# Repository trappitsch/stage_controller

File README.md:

# Stage controller

Multi-axis stage controller repo.

## Crates

The project is divided into multiple crates.
The following list gives an overview.

- `axis_control`: Controls a single axis of a stage.
- `rp2350`: Firmware for stage controller running on an RP2350.
- `icd`: Interface control document: How the device talks to the host.

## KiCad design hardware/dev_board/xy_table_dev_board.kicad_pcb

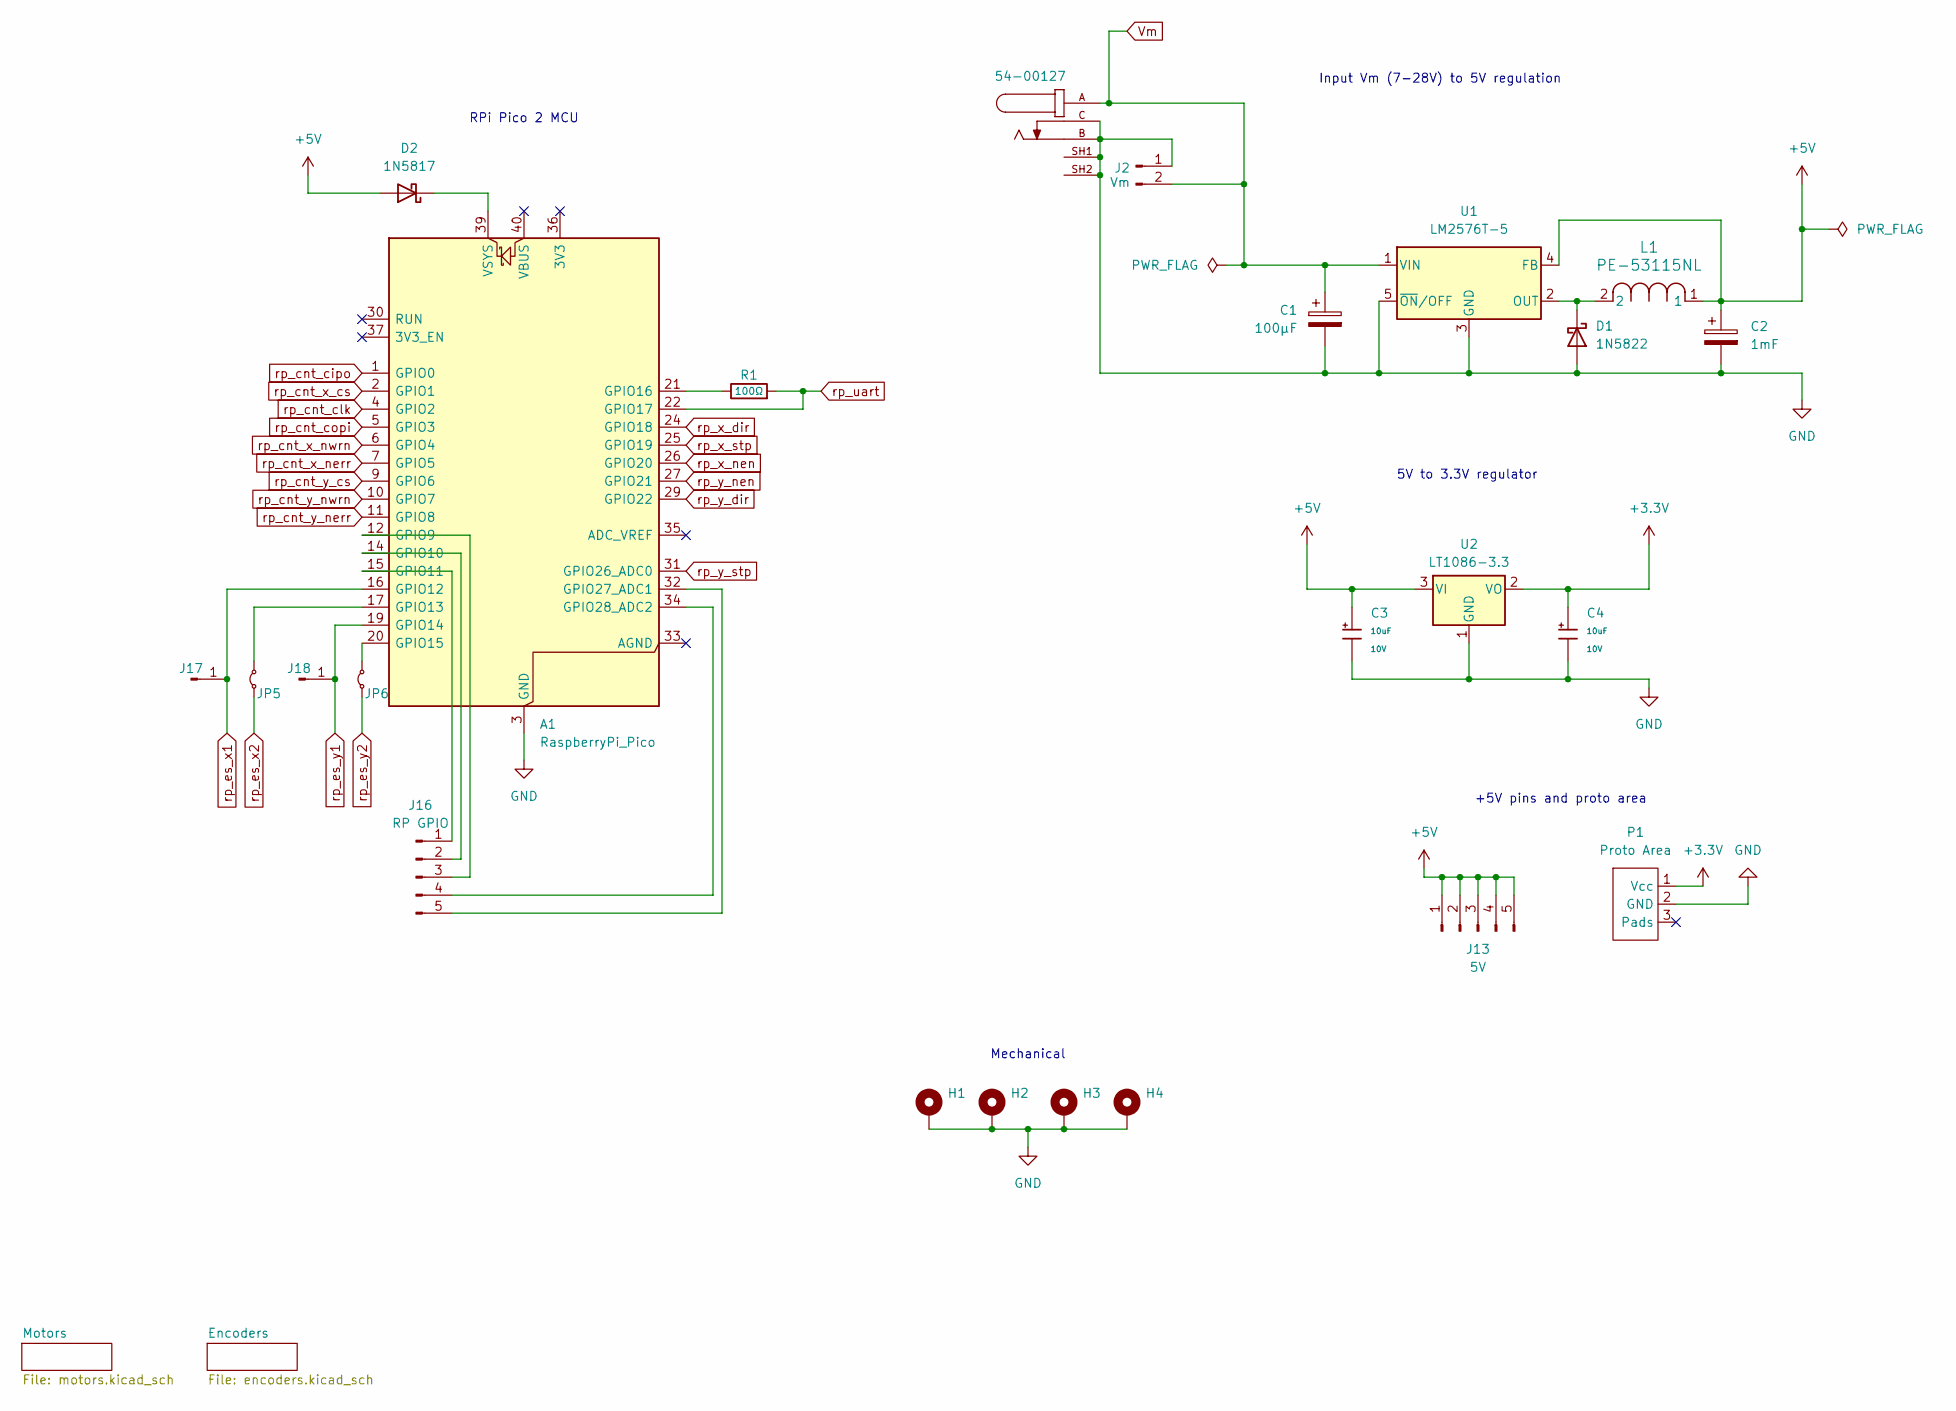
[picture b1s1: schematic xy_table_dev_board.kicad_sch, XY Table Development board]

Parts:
A1: RaspberryPi_Pico; RaspberryPi_Pico_Common_Unspecified
C1: 100µF; CP_Radial_D6.3mm_P2.50mm; Digikey 732-9215-1-ND
C2: 1mF; CP_Radial_D12.5mm_P5.00mm; Digikey 493-1322-ND
C3, C4: 10uF; C_1206_3216Metric_Pad1.33x1.80mm_HandSolder; Rated Voltage 10V; Digikey 478-11220-2-ND
D1: 1N5822; D_DO-201AD_P15.24mm_Horizontal; Digikey 497-11370-1-ND
D2: 1N5817; D_DO-41_SOD81_P10.16mm_Horizontal
H1, H2, H3, H4: MountingHole_Pad; MountingHole_3.2mm_M3_DIN965_Pad_TopBottom
J1: 54-00127; TENSILITY_54-00127; PARTREV A; Digikey 839-54-00127-ND
J2: Vm; PinHeader_1x02_P2.54mm_Vertical
J13: 5V; PinHeader_1x05_P2.54mm_Vertical
J16: RP GPIO; PinHeader_1x05_P2.54mm_Vertical
J17, J18: Conn_01x01_Pin; PinHeader_1x01_P2.54mm_Vertical
JP5, JP6: Jumper_2_Small_Bridged; TestPoint_2Pads_Pitch2.54mm_Drill0.8mm
L1: PE-53115NL; IND_PE-53115NL_PUL; Digikey 553-1566-5-ND
P1: Proto Area; proto_area_5x20_vcc_gnd
R1: 100Ω; R_1206_3216Metric_Pad1.30x1.75mm_HandSolder
U1: LM2576T-5; TO-220-5_Vertical; Digikey LM2576T-5.0/NOPB-ND
U2: LT1086-3.3; TO-220-3_Vertical

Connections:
+3.3V: C4.1, P1.1 (Vcc), U2.2 (VO); also elsewhere on the board
+5V: C2.1, C3.1, D2.2 (A), J13.1, J13.2, J13.3, J13.4, J13.5, L1.1, U1.4 (FB), U2.3 (VI); also elsewhere on the board
GND: A1.3 (GND), A1.8 (GND), A1.13 (GND), A1.18 (GND), A1.23 (GND), A1.28 (GND), A1.38 (GND), C1.2, C2.2, C3.2, C4.2, D1.2 (A), H1.1 (1_1), H2.1 (1_1), H3.1 (1_1), H4.1 (1_1), J1.B, J1.C, J1.SH1, J1.SH2, J2.1, P1.2 (GND), U1.3 (GND), U1.5 (~ON/OFF), U2.1 (GND); also elsewhere on the board
unnamed: A1.12 (GPIO9), J16.3
unnamed: A1.14 (GPIO10), J16.2
unnamed: A1.15 (GPIO11), J16.1
unnamed: A1.17 (GPIO13), JP5.2 (B)
unnamed: A1.20 (GPIO15), JP6.2 (B)
unnamed: A1.21 (GPIO16), R1.1
unnamed: A1.32 (GPIO27_ADC1), J16.5
unnamed: A1.34 (GPIO28_ADC2), J16.4
unnamed: A1.39 (VSYS), D2.1 (K)
unnamed: D1.1 (K), L1.2, U1.2 (OUT)
Vm: C1.1, J1.A, J2.2, U1.1 (VIN); also elsewhere on the board
rp_cnt_cipo: A1.1 (GPIO0); also elsewhere on the board
rp_cnt_clk: A1.4 (GPIO2); also elsewhere on the board
rp_cnt_copi: A1.5 (GPIO3); also elsewhere on the board
rp_cnt_x_cs: A1.2 (GPIO1); also elsewhere on the board
rp_cnt_x_nerr: A1.7 (GPIO5); also elsewhere on the board
rp_cnt_x_nwrn: A1.6 (GPIO4); also elsewhere on the board
rp_cnt_y_cs: A1.9 (GPIO6); also elsewhere on the board
rp_cnt_y_nerr: A1.11 (GPIO8); also elsewhere on the board
rp_cnt_y_nwrn: A1.10 (GPIO7); also elsewhere on the board
rp_es_x1: A1.16 (GPIO12), J17.1 (Pin_1_1); also elsewhere on the board
rp_es_x2: JP5.1 (A); also elsewhere on the board
rp_es_y1: A1.19 (GPIO14), J18.1 (Pin_1_1); also elsewhere on the board
rp_es_y2: JP6.1 (A); also elsewhere on the board
rp_uart: A1.22 (GPIO17), R1.2; also elsewhere on the board
rp_x_dir: A1.24 (GPIO18); also elsewhere on the board
rp_x_nen: A1.26 (GPIO20); also elsewhere on the board
rp_x_stp: A1.25 (GPIO19); also elsewhere on the board
rp_y_dir: A1.29 (GPIO22); also elsewhere on the board
rp_y_nen: A1.27 (GPIO21); also elsewhere on the board
rp_y_stp: A1.31 (GPIO26_ADC0); also elsewhere on the board

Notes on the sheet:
RPi Pico 2 MCU
Input Vm (7-28V) to 5V regulation
+5V pins and proto area
5V to 3.3V regulator
Mechanical

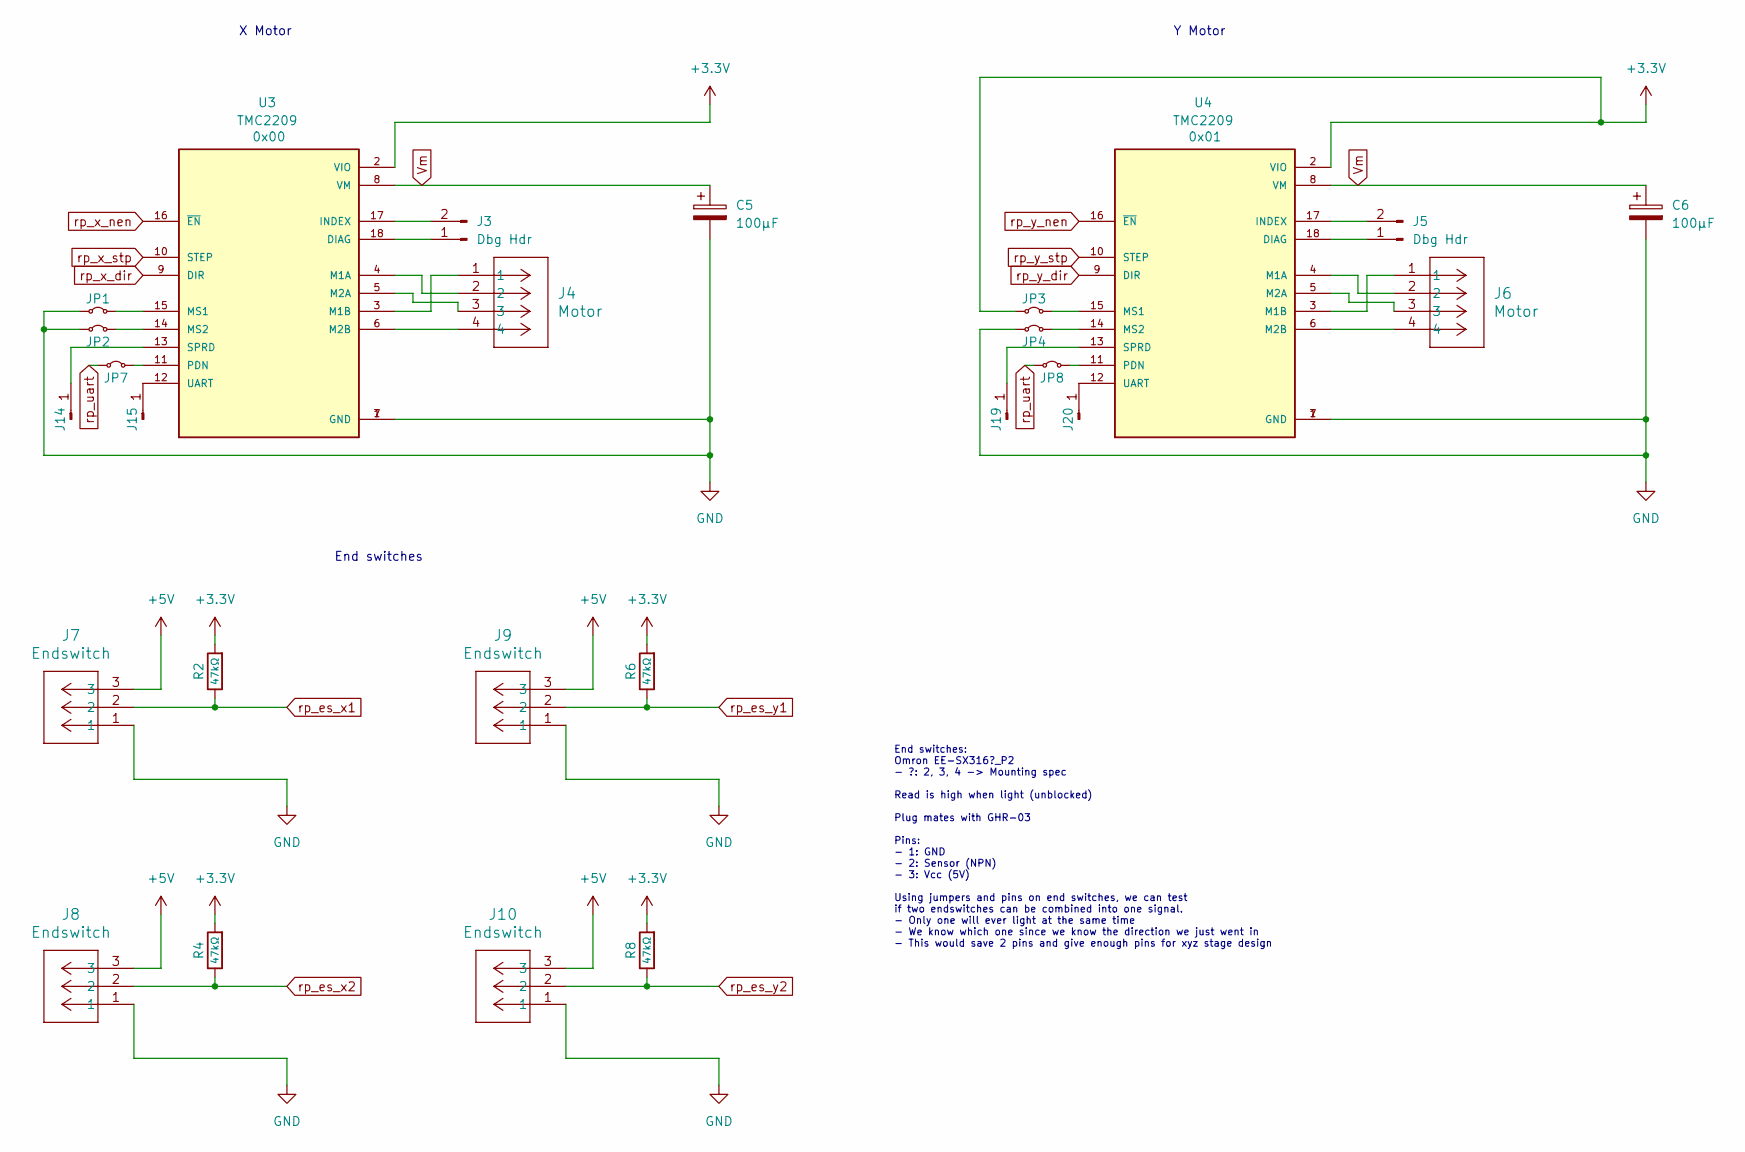
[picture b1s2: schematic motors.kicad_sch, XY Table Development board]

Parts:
C5, C6: 100µF; CP_Radial_D6.3mm_P2.50mm; Digikey 732-9215-1-ND
J3, J5: Dbg Hdr; PinHeader_1x02_P2.54mm_Vertical
J4, J6: Motor; CONN_A-6373-04A_MOL; Digikey WM2702-ND
J7, J8, J9, J10: Endswitch; CONN_A-6373-03A_MOL; Digikey WM2701-ND
J14, J15, J19, J20: Conn_01x01_Pin; PinHeader_1x01_P2.54mm_Vertical
JP1, JP2, JP3, JP4, JP7, JP8: Jumper_2_Small_Bridged; TestPoint_2Pads_Pitch2.54mm_Drill0.8mm
R2, R4, R6, R8: 47kΩ; R_Axial_DIN0207_L6.3mm_D2.5mm_P7.62mm_Horizontal; Digikey CF18JT47K0TR-ND
U3, U4: TMC2209; MODULE_TMC2209_SILENTSTEPSTICK; PARTREV 1.20

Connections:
+3.3V: JP3.1 (A), R2.2, R4.2, R6.2, R8.2, U3.2 (VIO), U4.2 (VIO); also elsewhere on the board
+5V: J7.3, J8.3, J9.3, J10.3; also elsewhere on the board
GND: C5.2, C6.2, J7.1, J8.1, J9.1, J10.1, JP1.1 (A), JP2.1 (A), JP4.1 (A), U3.1 (GND), U3.7 (GND), U4.1 (GND), U4.7 (GND); also elsewhere on the board
unnamed: J3.1, U3.18 (DIAG)
unnamed: J3.2, U3.17 (INDEX)
unnamed: J5.1, U4.18 (DIAG)
unnamed: J5.2, U4.17 (INDEX)
unnamed: J14.1 (Pin_1_1), U3.13 (SPRD)
unnamed: J15.1 (Pin_1_1), U3.12 (UART)
unnamed: J19.1 (Pin_1_1), U4.13 (SPRD)
unnamed: J20.1 (Pin_1_1), U4.12 (UART)
unnamed: JP1.2 (B), U3.15 (MS1)
unnamed: JP2.2 (B), U3.14 (MS2)
unnamed: JP3.2 (B), U4.15 (MS1)
unnamed: JP4.2 (B), U4.14 (MS2)
unnamed: JP7.2 (B), U3.11 (PDN)
unnamed: JP8.2 (B), U4.11 (PDN)
unnamed: J4.2, U3.4 (M1A)
unnamed: J4.1, U3.3 (M1B)
unnamed: J4.3, U3.5 (M2A)
unnamed: J4.4, U3.6 (M2B)
unnamed: J6.2, U4.4 (M1A)
unnamed: J6.1, U4.3 (M1B)
unnamed: J6.3, U4.5 (M2A)
unnamed: J6.4, U4.6 (M2B)
Vm: C5.1, C6.1, U3.8 (VM), U4.8 (VM); also elsewhere on the board
rp_es_x1: J7.2, R2.1; also elsewhere on the board
rp_es_x2: J8.2, R4.1; also elsewhere on the board
rp_es_y1: J9.2, R6.1; also elsewhere on the board
rp_es_y2: J10.2, R8.1; also elsewhere on the board
rp_uart: JP7.1 (A), JP8.1 (A); also elsewhere on the board
rp_x_dir: U3.9 (DIR); also elsewhere on the board
rp_x_nen: U3.16 (~EN); also elsewhere on the board
rp_x_stp: U3.10 (STEP); also elsewhere on the board
rp_y_dir: U4.9 (DIR); also elsewhere on the board
rp_y_nen: U4.16 (~EN); also elsewhere on the board
rp_y_stp: U4.10 (STEP); also elsewhere on the board

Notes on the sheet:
Y Motor
End switches: Omron EE-SX316?_P2 - ?: 2, 3, 4 -> Mounting spec Read is high when light (unblocked) Plug mates with GHR-03 Pins: - 1: GND - 2: Sensor (NPN) - 3: Vcc (5V) Using jumpers and pins on end switches, we can test if two endswitches can be combined into one signal. - Only one will ever light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
End switches
X Motor

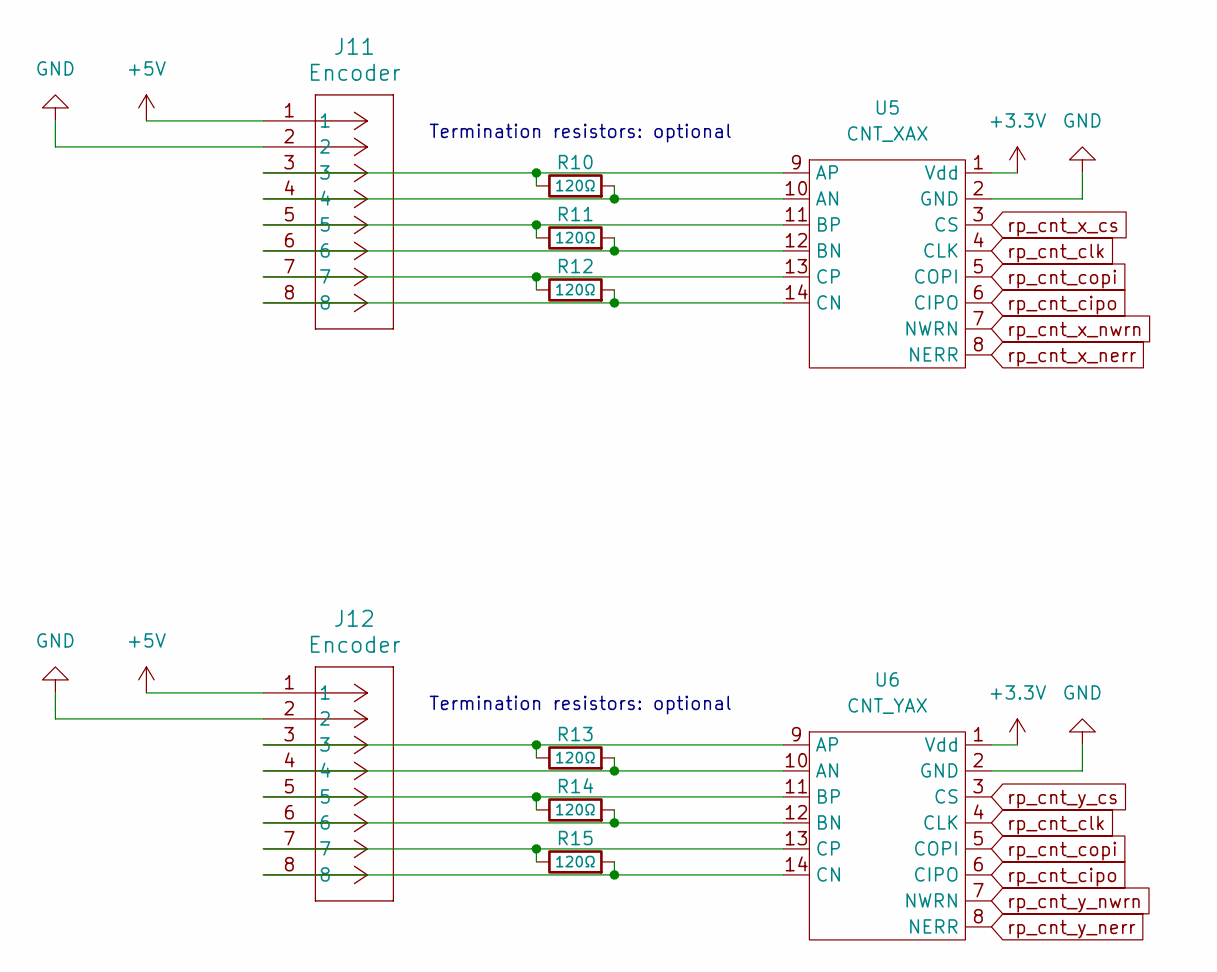
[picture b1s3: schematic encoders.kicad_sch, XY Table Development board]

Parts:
J11, J12: Encoder; CONN_A-6373-08A_MOL; Digikey 900-0022112082-ND
R10, R11, R12, R13, R14, R15: 120Ω; R_Axial_DIN0207_L6.3mm_D2.5mm_P7.62mm_Horizontal
U5: CNT_XAX; iC-MD_brd_5VSig_3.3Vcc
U6: CNT_YAX; iC-MD_brd_5VSig_3.3Vcc

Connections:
+3.3V: U5.1 (Vdd), U6.1 (Vdd); also elsewhere on the board
+5V: J11.1, J12.1; also elsewhere on the board
GND: J11.2, J12.2, U5.2 (GND), U6.2 (GND); also elsewhere on the board
unnamed: J11.4, R10.2, U5.10 (AN)
unnamed: J11.3, R10.1, U5.9 (AP)
unnamed: J11.6, R11.2, U5.12 (BN)
unnamed: J11.5, R11.1, U5.11 (BP)
unnamed: J11.8, R12.2, U5.14 (CN)
unnamed: J11.7, R12.1, U5.13 (CP)
unnamed: J12.4, R13.2, U6.10 (AN)
unnamed: J12.3, R13.1, U6.9 (AP)
unnamed: J12.6, R14.2, U6.12 (BN)
unnamed: J12.5, R14.1, U6.11 (BP)
unnamed: J12.8, R15.2, U6.14 (CN)
unnamed: J12.7, R15.1, U6.13 (CP)
rp_cnt_cipo: U5.6 (CIPO), U6.6 (CIPO); also elsewhere on the board
rp_cnt_clk: U5.4 (CLK), U6.4 (CLK); also elsewhere on the board
rp_cnt_copi: U5.5 (COPI), U6.5 (COPI); also elsewhere on the board
rp_cnt_x_cs: U5.3 (CS); also elsewhere on the board
rp_cnt_x_nerr: U5.8 (NERR); also elsewhere on the board
rp_cnt_x_nwrn: U5.7 (NWRN); also elsewhere on the board
rp_cnt_y_cs: U6.3 (CS); also elsewhere on the board
rp_cnt_y_nerr: U6.8 (NERR); also elsewhere on the board
rp_cnt_y_nwrn: U6.7 (NWRN); also elsewhere on the board

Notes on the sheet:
Termination resistors: optional

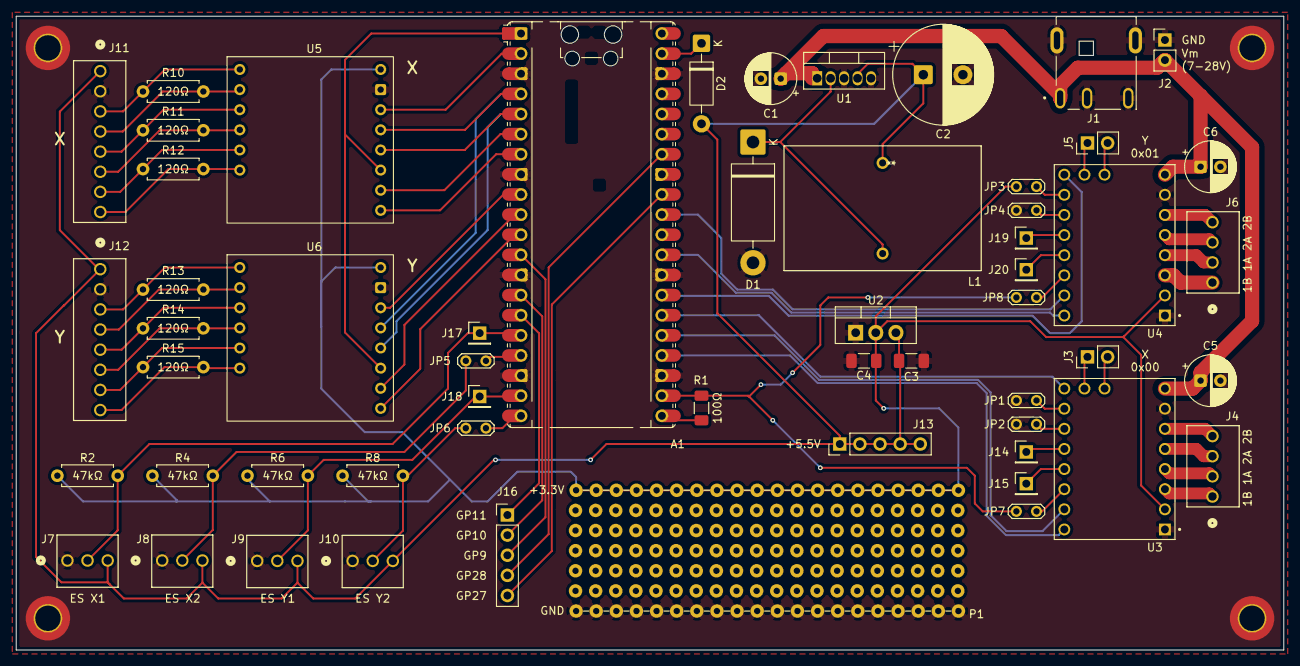
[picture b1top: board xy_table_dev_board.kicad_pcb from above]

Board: 2 copper layers, 160.0 x 80.0 mm, 60 parts (0 on the bottom side), 68 nets.
